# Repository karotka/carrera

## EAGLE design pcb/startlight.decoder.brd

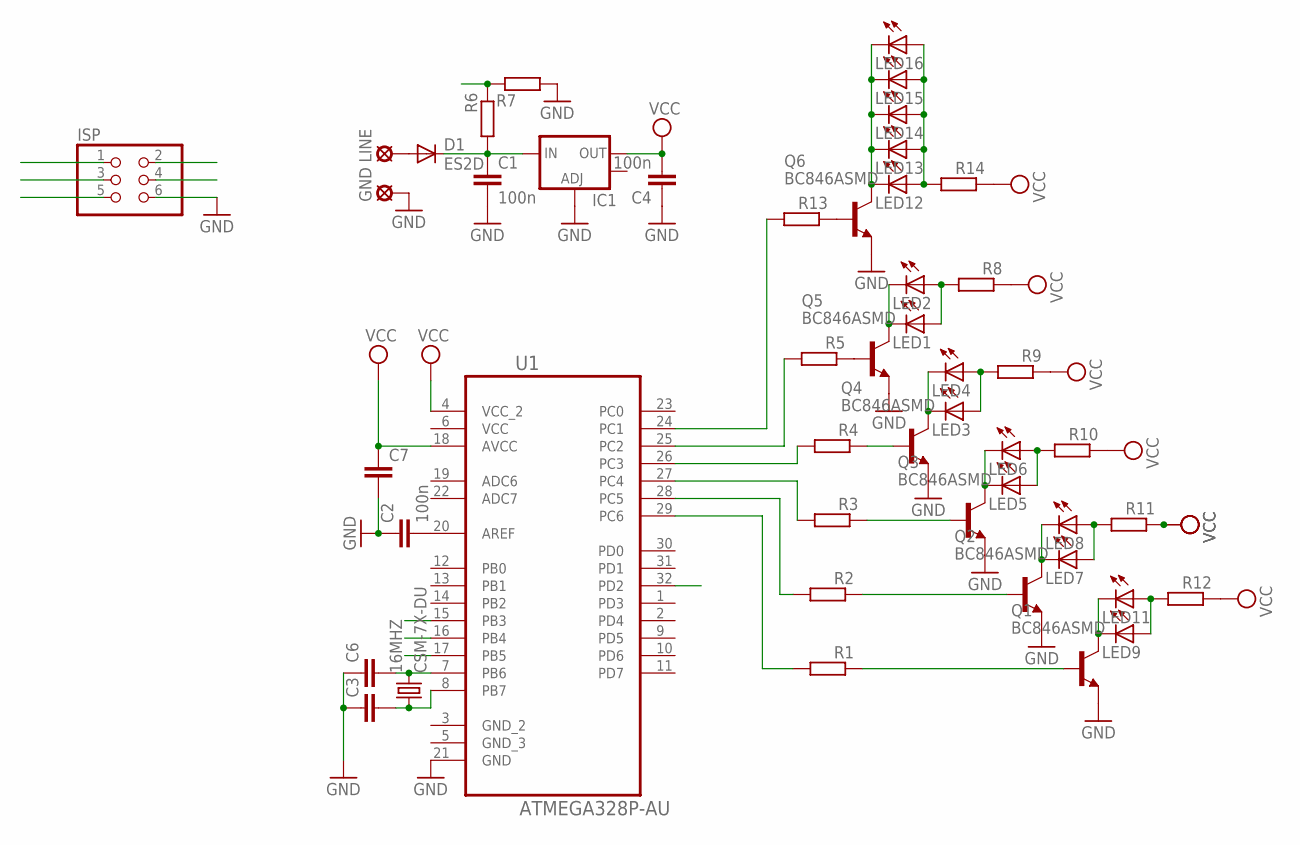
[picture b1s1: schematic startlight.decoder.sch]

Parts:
16MHZ: CSM-7X-DU
C1: 100n; C025-040X050
C2, C4: 100n; C1206
C3, C6: C-EUC0805K; C0805K
C7: C-EU025-040X050; C025-040X050
D1: ES2D; SMB
GND: SE11
IC1: V_REG_LM1117SOT223; SOT223
ISP: PINHD-2X3; 2X03
LED1, LED2, LED3, LED4, LED5, LED6, LED7, LED8, LED9, LED11, LED12, LED13, LED14, LED15, LED16: LED5MM
LINE: SE11
Q1, Q2, Q3, Q4, Q5, Q6: BC846ASMD; SOT23
R1, R2, R3, R4, R5, R6, R7, R8, R9, R10, R11, R12, R13, R14: R-EU_R1206; R1206
U1: ATMEGA328P-AU; QFP80P900X900X120-32N

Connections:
GND: C1.2, C2.1, C3.1, C4.1, C6.1, C7.2, GND.MP, IC1.1 (ADJ), ISP.6, Q1.2 (E), Q2.2 (E), Q3.2 (E), Q4.2 (E), Q5.2 (E), Q6.2 (E), R7.2, U1.21 (GND)
INT0: R6.1, R7.1, U1.32 (PD2)
MISO: ISP.1, U1.16 (PB4)
MOSI: ISP.4, U1.15 (PB3)
unnamed: R5.2, U1.25 (PC2)
unnamed: R4.2, U1.26 (PC3)
unnamed: R3.2, U1.27 (PC4)
unnamed: R2.2, U1.28 (PC5)
unnamed: R1.2, U1.29 (PC6)
unnamed: Q5.1 (B), R5.1
unnamed: Q4.1 (B), R4.1
unnamed: Q3.1 (B), R3.1
unnamed: Q2.1 (B), R2.1
unnamed: Q1.1 (B), R1.1
unnamed: D1.A, LINE.MP
unnamed: C1.1, D1.C, IC1.3 (IN), R6.2
unnamed: C2.2, U1.20 (AREF)
unnamed: LED1.K (C), LED2.K (C), Q5.3 (C)
unnamed: LED3.K (C), LED4.K (C), Q4.3 (C)
unnamed: LED1.A, LED2.A, R8.2
unnamed: LED5.K (C), LED6.K (C), Q3.3 (C)
unnamed: LED3.A, LED4.A, R9.2
unnamed: LED7.K (C), LED8.K (C), Q2.3 (C)
unnamed: LED5.A, LED6.A, R10.2
unnamed: LED9.K (C), LED11.K (C), Q1.3 (C)
unnamed: LED7.A, LED8.A, R11.2
unnamed: LED9.A, LED11.A, R12.2
unnamed: Q6.1 (B), R13.1
unnamed: R13.2, U1.24 (PC1)
unnamed: LED12.K (C), LED13.K (C), LED14.K (C), LED15.K (C), LED16.K (C), Q6.3 (C)
unnamed: LED12.A, LED13.A, LED14.A, LED15.A, LED16.A, R14.2
unnamed: 16MHZ.2, C6.2, U1.7 (PB6)
unnamed: 16MHZ.1, C3.2, U1.8 (PB7)
RESET: ISP.5
SCK: ISP.3, U1.17 (PB5)
VCC: C4.2, C7.1, IC1.2 (OUT), ISP.2, R8.1, R9.1, R10.1, R11.1, R12.1, R14.1, U1.4 (VCC_2), U1.6 (VCC), U1.18 (AVCC)

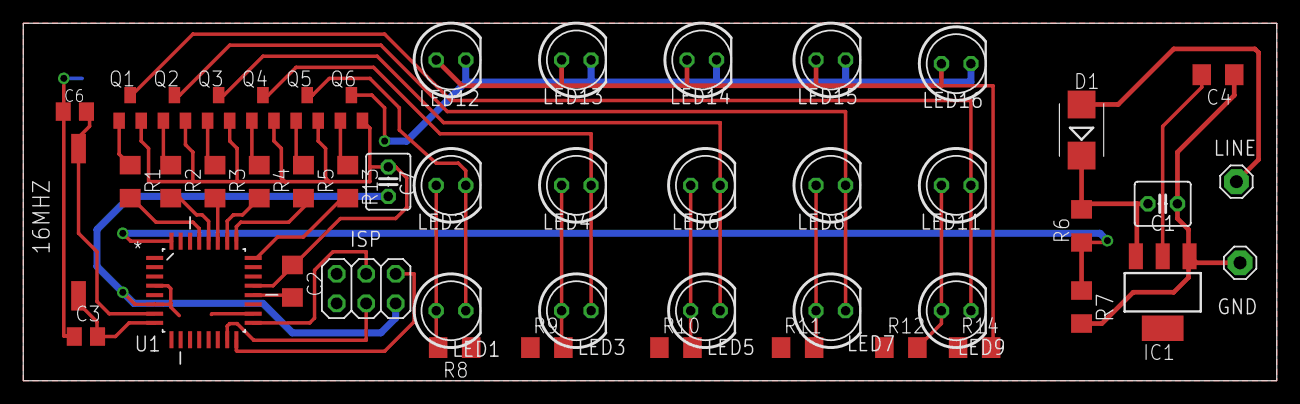
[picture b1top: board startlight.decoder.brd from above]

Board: 2 copper layers, 107.9 x 30.8 mm, 48 parts (0 on the bottom side), 35 nets.

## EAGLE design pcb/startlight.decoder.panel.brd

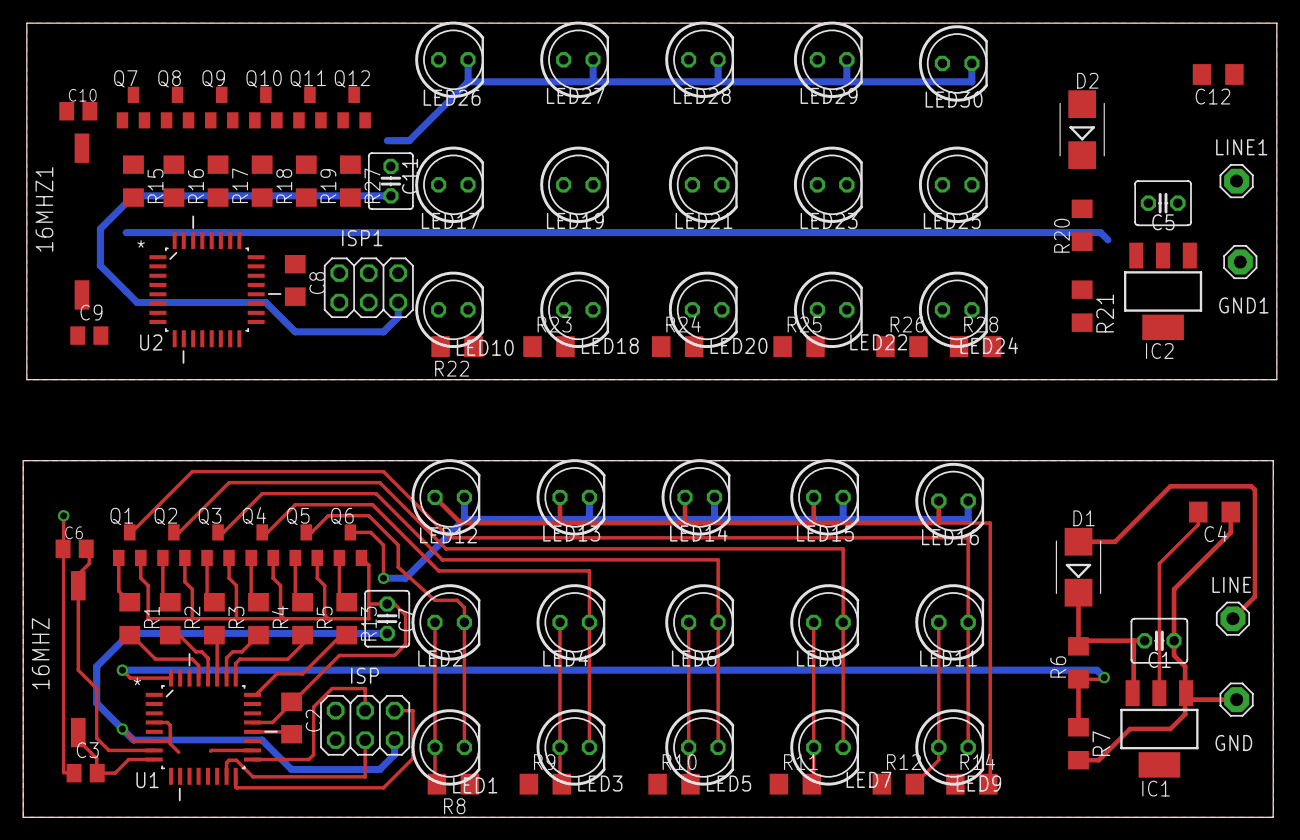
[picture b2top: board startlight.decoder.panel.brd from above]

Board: 2 copper layers, 108.2 x 68.6 mm, 96 parts (0 on the bottom side), 70 nets.

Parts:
16MHZ, 16MHZ1: CSM-7X-DU
C1, C5: 100n; C025-040X050
C2, C4, C8, C12: 100n; C1206
C3, C6, C9, C10: C0805K
C7, C11: C025-040X050
D1, D2: ES2D; SMB
GND, GND1: SE11
IC1, IC2: SOT223
ISP, ISP1: 2X03
LED1, LED2, LED3, LED4, LED5, LED6, LED7, LED8, LED9, LED10, LED11, LED12, LED13, LED14, LED15, LED16, LED17, LED18, LED19, LED20, LED21, LED22, LED23, LED24, LED25, LED26, LED27, LED28, LED29, LED30: LED5MM
LINE, LINE1: SE11
Q1, Q2, Q3, Q4, Q5, Q6, Q7, Q8, Q9, Q10, Q11, Q12: BC846ASMD; SOT23
R1, R2, R3, R4, R5, R6, R7, R8, R9, R10, R11, R12, R13, R14, R15, R16, R17, R18, R19, R20, R21, R22, R23, R24, R25, R26, R27, R28: R1206
U1, U2: ATMEGA328P-AU; QFP80P900X900X120-32N

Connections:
GND: C1.2, C2.1, C3.1, C4.1, C6.1, C7.2, GND.MP, IC1.1, ISP.6, Q1.2, Q2.2, Q3.2, Q4.2, Q5.2, Q6.2, R7.2, U1.21
GND2: C5.2, C8.1, C9.1, C10.1, C11.2, C12.1, GND1.MP, IC2.1, ISP1.6, Q7.2, Q8.2, Q9.2, Q10.2, Q11.2, Q12.2, R21.2, U2.21
INT0: R6.1, R7.1, U1.32
INT2: R20.1, R21.1, U2.32
MISO: ISP.1, U1.16
MISO1: ISP1.1, U2.16
MOSI: ISP.4, U1.15
MOSI1: ISP1.4, U2.15
unnamed: R5.2, U1.25
unnamed: R4.2, U1.26
unnamed: R3.2, U1.27
unnamed: R2.2, U1.28
unnamed: R1.2, U1.29
unnamed: Q5.1, R5.1
unnamed: Q4.1, R4.1
unnamed: Q3.1, R3.1
unnamed: Q2.1, R2.1
unnamed: Q1.1, R1.1
unnamed: D1.A, LINE.MP
unnamed: C1.1, D1.C, IC1.3, R6.2
unnamed: C2.2, U1.20
unnamed: LED1.K, LED2.K, Q5.3
unnamed: LED3.K, LED4.K, Q4.3
unnamed: LED1.A, LED2.A, R8.2
unnamed: LED5.K, LED6.K, Q3.3
unnamed: LED3.A, LED4.A, R9.2
unnamed: LED7.K, LED8.K, Q2.3
unnamed: LED5.A, LED6.A, R10.2
unnamed: LED9.K, LED11.K, Q1.3
unnamed: LED7.A, LED8.A, R11.2
unnamed: LED9.A, LED11.A, R12.2
unnamed: Q6.1, R13.1
unnamed: R13.2, U1.24
unnamed: LED12.K, LED13.K, LED14.K, LED15.K, LED16.K, Q6.3
unnamed: LED12.A, LED13.A, LED14.A, LED15.A, LED16.A, R14.2
unnamed: 16MHZ1.2, C10.2, U2.7
unnamed: 16MHZ.2, C6.2, U1.7
unnamed: 16MHZ.1, C3.2, U1.8
unnamed: 16MHZ1.1, C9.2, U2.8
unnamed: R19.2, U2.25
unnamed: R18.2, U2.26
unnamed: R17.2, U2.27
unnamed: R16.2, U2.28
unnamed: R15.2, U2.29
unnamed: Q11.1, R19.1
unnamed: Q10.1, R18.1
unnamed: Q9.1, R17.1
unnamed: Q8.1, R16.1
unnamed: Q7.1, R15.1
unnamed: C5.1, D2.C, IC2.3, R20.2
unnamed: D2.A, LINE1.MP
unnamed: LED10.K, LED17.K, Q11.3
unnamed: LED18.K, LED19.K, Q10.3
unnamed: LED20.K, LED21.K, Q9.3
unnamed: LED22.K, LED23.K, Q8.3
unnamed: LED24.K, LED25.K, Q7.3
unnamed: LED10.A, LED17.A, R22.2
unnamed: LED18.A, LED19.A, R23.2
unnamed: LED20.A, LED21.A, R24.2
unnamed: LED22.A, LED23.A, R25.2
unnamed: LED24.A, LED25.A, R26.2
unnamed: Q12.1, R27.1
unnamed: R27.2, U2.24
unnamed: LED26.K, LED27.K, LED28.K, LED29.K, LED30.K, Q12.3
unnamed: LED26.A, LED27.A, LED28.A, LED29.A, LED30.A, R28.2
unnamed: C8.2, U2.20
SCK: ISP.3, U1.17
SCK1: ISP1.3, U2.17
VCC: C4.2, C7.1, IC1.2, ISP.2, R8.1, R9.1, R10.1, R11.1, R12.1, R14.1, U1.4, U1.6, U1.18
VCC1: C11.1, C12.2, IC2.2, ISP1.2, R22.1, R23.1, R24.1, R25.1, R26.1, R28.1, U2.4, U2.6, U2.18

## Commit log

2016-01-27 bugfix
2016-02-07 final

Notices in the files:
parts and their libraries:
sparkfun: Licensing: CC v3.0 Share-Alike You are welcome to use this library for commercial purposes.
